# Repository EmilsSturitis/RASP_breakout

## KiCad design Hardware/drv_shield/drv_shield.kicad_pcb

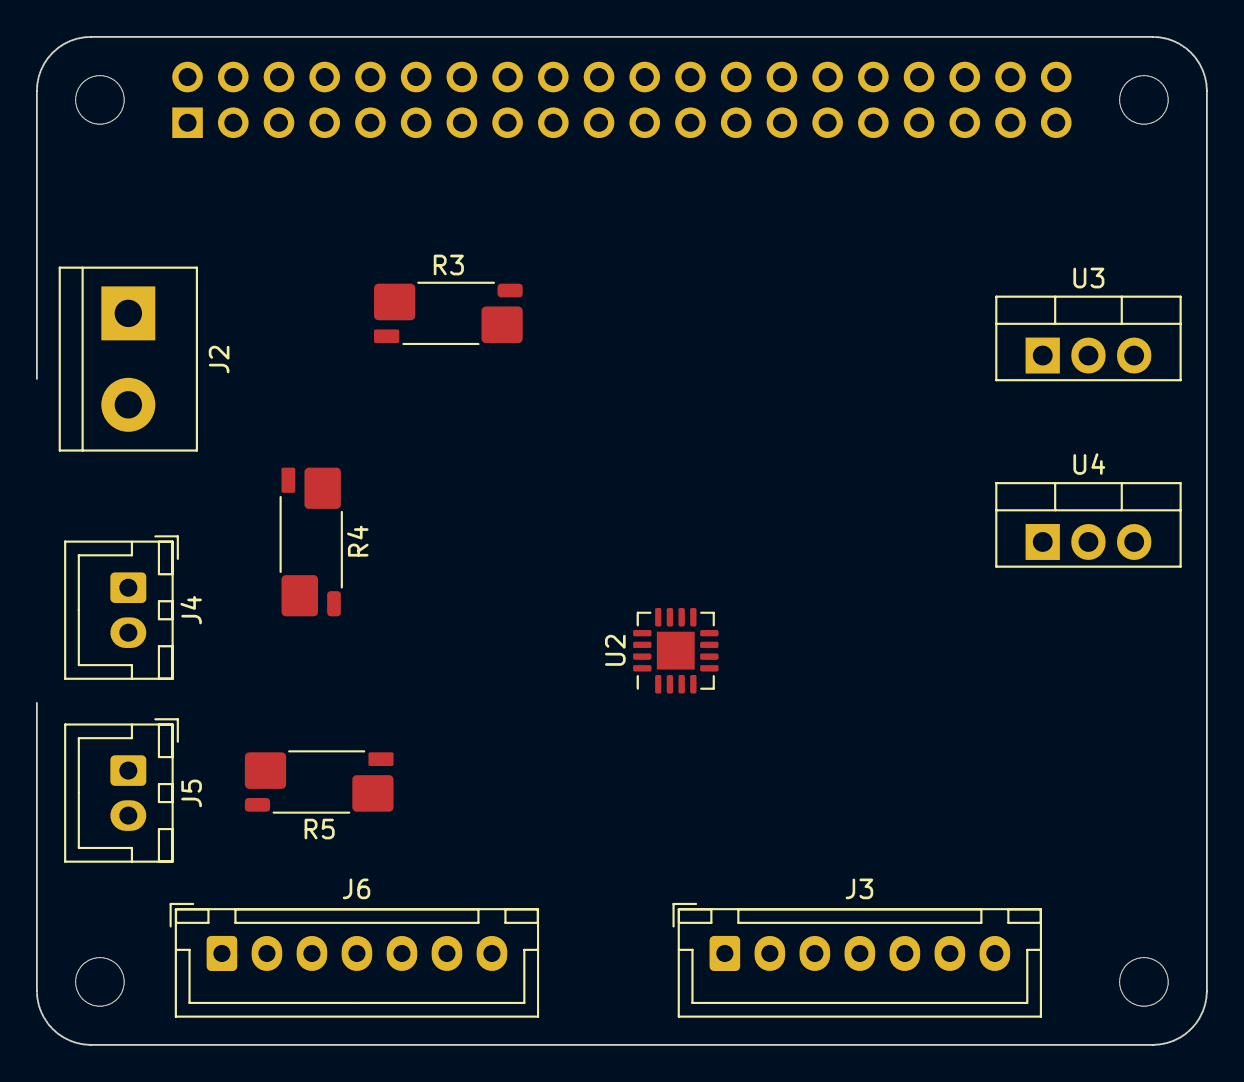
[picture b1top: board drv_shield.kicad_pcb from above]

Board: 2 copper layers, 65.0 x 56.0 mm, 16 parts (1 on the bottom side), 25 nets, no tracks yet.

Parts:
J1: GPIO; PinSocket_2x20_P2.54mm_Vertical
J2: Conn_01x02; TerminalBlock_bornier-2_P5.08mm
J3, J6: Conn_01x07; JST_XH_B7B-XH-A_1x07_P2.50mm_Vertical
J4, J5: Conn_01x02; JST_XH_B2B-XH-A_1x02_P2.50mm_Vertical
MH1, MH2, MH3, MH4: MountingHole_2.7mm_M2.5
R3, R4, R5: R_Shunt; R_Shunt_Vishay_WSK2512_6332Metric_T1.19mm
U2: INA3221; Texas_RGV_S-PVQFN-N16_EP2.1x2.1mm
U3, U4: LM7805_TO220; TO-220-3_Vertical

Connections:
+3V3: J1.1, J1.17
+5V: J1.2, J1.4, U3.3 (VO), U4.3 (VO)
/DRV_ENA: J1.11, J3.1
/DRV_ENB_2: J1.37, J6.6
/DRV_IN_1: J1.13, J3.2
/DRV_IN_3_2: J1.33, J6.4
/DRV_IN_4_2: J1.35, J6.5
/GPIO[9]/SPI0.MISO: J1.21, J3.5
/GPIO[10]/SPI0.MOSI: J1.19, J3.4
/GPIO[11]/SPI0.SCLK: J1.23, J3.6
/GPIO[16]: J1.36, J6.1
/GPIO[20]/PCM.DIN: J1.38, J6.2
/GPIO[21]/PCM.DOUT: J1.40, J6.3
/GPIO[22]: J1.15, J3.3
GND: J1.6, J1.9, J1.14, J1.20, J1.25, J1.30, J1.34, J1.39, J2.2, J3.7, J4.2, J5.2, J6.7, U2.3 (GND), U3.2 (GND), U4.2 (GND)
unnamed: J2.1, R3.1, R4.1, R5.1, U2.16 (VPU)
unnamed: J4.1, R4.4
unnamed: J5.1, R5.4
unnamed: R3.2, U2.2 (IN+3)
unnamed: R3.3, U2.1 (IN-3)
unnamed: R3.4, U3.1 (VI), U4.1 (VI)
unnamed: R4.2, U2.12 (IN+1)
unnamed: R4.3, U2.11 (IN-1)
unnamed: R5.2, U2.15 (IN+2)
unnamed: R5.3, U2.14 (IN-2)
